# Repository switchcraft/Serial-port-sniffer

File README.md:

# Serial-port-sniffer
A RS232 serial port sniffer with USB interface.

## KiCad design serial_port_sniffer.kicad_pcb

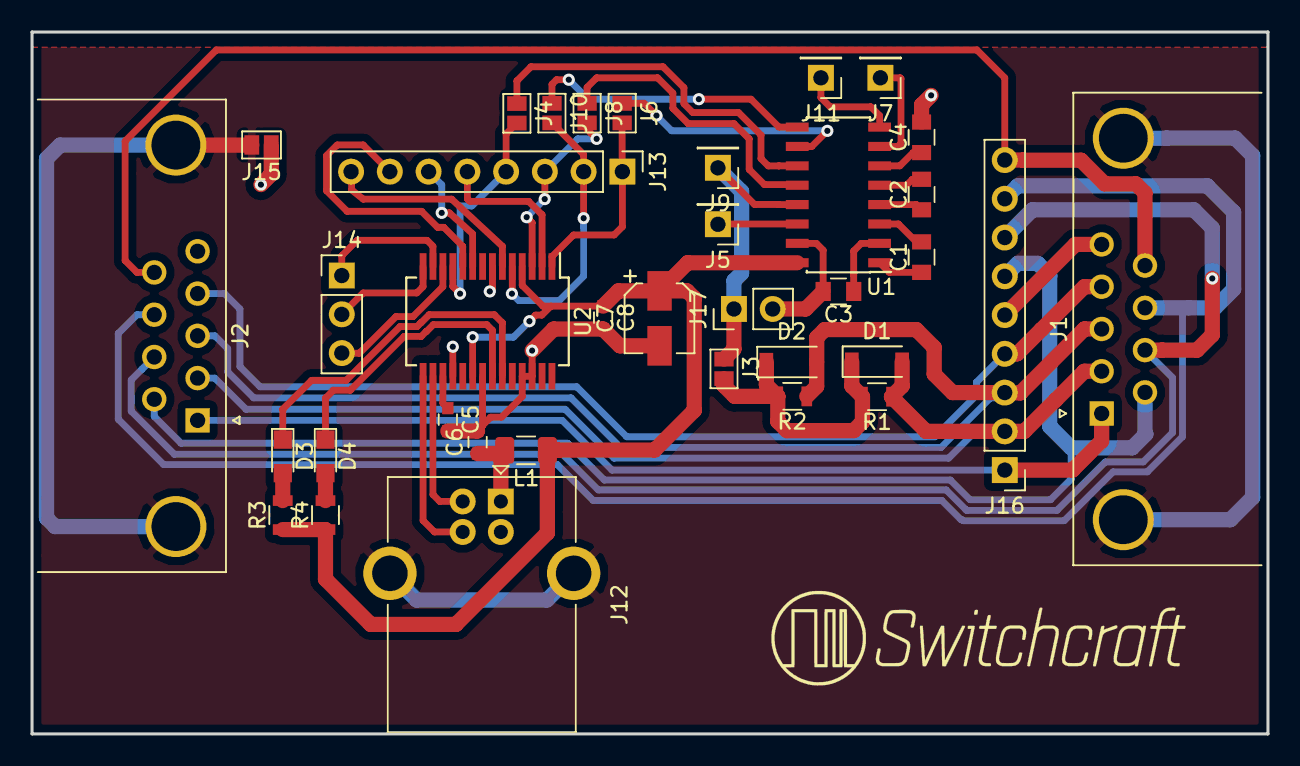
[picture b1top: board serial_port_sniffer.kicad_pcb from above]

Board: 2 copper layers, 81.0 x 46.0 mm, 36 parts (0 on the bottom side), 45 nets.

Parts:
C1, C2, C3, C4: 1u; C_0805
C5, C8: 100n; C_0603
C6: 10n; C_0603
C7: 4u7; CP_Elec_4x5.3
D1, D2: LL4148; D_SOD-123
D3, D4: LED; LED_0805
J1: DB9_Male_MountingHoles; DSUB-9_Male_Horizontal_P2.77x2.84mm_EdgePinOffset7.70mm_Hou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
J2: DB9_Female_MountingHoles; DSUB-9_Female_Horizontal_P2.77x2.84mm_EdgePinOffset7.70mm_H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
J3, J4, J6, J8, J10, J15: GS2
J5, J7, J9, J11: Conn_01x01; Pin_Header_Straight_1x01_Pitch2.54mm
J12: USB_B; USB_B_OST_USB-B1HSxx_Horizontal
J13: Conn_01x08; Pin_Header_Straight_1x08_Pitch2.54mm
J14: Conn_01x03; Pin_Header_Straight_1x03_Pitch2.54mm
J16: Conn_01x09; Pin_Header_Straight_1x09_Pitch2.54mm
J17: Conn_01x02; Pin_Header_Straight_1x02_Pitch2.54mm
L1: Ferrite_Bead; L_1206_3216Metric
R1, R2: 4k7; R_0805
R3, R4: 1k; R_0805
U1: MAX232; SOIC-16_3.9x9.9mm_P1.27mm
U2: FT232RL; SSOP-28_5.3x10.2mm_Pitch0.65mm

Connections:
GND: C3.2, C4.2, C5.2, C6.2, C7.2, C8.2, J1.5, J2.5, J12.4, J15.1, J16.5, J17.2, U1.15, U2.7, U2.18, U2.21, U2.25, U2.26
GNDD: J1.0, J2.0, J12.5, J15.2
unnamed: C1.1, U1.1
unnamed: C1.2, U1.3
unnamed: C2.1, U1.4
unnamed: C2.2, U1.5
unnamed: C3.1, U1.2
unnamed: C4.1, U1.6
unnamed: C5.1, U2.17
unnamed: C6.1, J12.1, L1.2
unnamed: D1.1, D2.1, J3.2, R1.2, R2.2
unnamed: D1.2, J1.2, J2.2, J16.2, R1.1
unnamed: D2.2, J1.3, J2.3, J16.3, R2.1
unnamed: D3.1, U2.23
unnamed: D3.2, R3.2
unnamed: D4.1, U2.22
unnamed: D4.2, R4.2
unnamed: J1.1, J2.1, J16.1
unnamed: J1.4, J2.4, J16.4
unnamed: J1.6, J2.6, J16.6
unnamed: J1.7, J2.7, J16.7
unnamed: J1.8, J2.8, J16.8
unnamed: J1.9, J2.9, J16.9
unnamed: J4.1, U1.11
unnamed: J5.1, U1.14
unnamed: J6.1, U1.10
unnamed: J7.1, U1.7
unnamed: J8.1, U1.12
unnamed: J10.1, U1.9
unnamed: J10.2, J13.2, U2.5
unnamed: J11.1, U1.8
unnamed: J12.2, U2.16
unnamed: J12.3, U2.15
unnamed: J6.2, J13.1, U2.1
unnamed: J8.2, J13.3, U2.3
unnamed: J4.2, J13.4, U2.11
unnamed: J13.5, U2.2
unnamed: J13.6, U2.9
unnamed: J13.7, U2.10
unnamed: J13.8, U2.6
unnamed: J14.1, U2.13
unnamed: J14.2, U2.14
unnamed: J14.3, U2.12
Sniffer: J3.1, J9.1, J17.1, U1.13
VCC: C7.1, C8.1, L1.1, R3.1, R4.1, U1.16, U2.4, U2.20

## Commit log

2018-10-08 Finished PCB layout
2018-10-08 Added 3d image of PCB
